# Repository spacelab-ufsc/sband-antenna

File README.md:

<h1 align="center">
	S-Band Antenna Project
	<br>
</h1>

<p align="center">

</p>

<details>
    <summary><b>Summary</b></summary>
    <ol>
        <li>
            <a href="#overview">Overview</a>
        </li>
        <li>
            <a href="#repository-organization">Repository Organization</a>
        </li>
        <li>
            <a href="#license">License</a>
        </li>
        <li>
            <a href="#releases">Releases</a>
        </li>
        <li>
            <a href="#notes">Notes</a>
        </li>
        <li>
            <a href="#references">References</a>
        </li>
    </ol>
</details>

## Overview
​The S-Band Antenna project consists of developing an antenna for the S-Band frequency (2.200-2.290 GHz), which its initial goal is to be used in a mission of Radio Occultation for the downlink of data.​

<!-- 

-->

<p align="center">

</p>

## Repository Organization
`hardware`: Main files of the hardware of the GNSS Active Antenna project.

`docs`: Technical documentation (including user guide and datasheet)

## License
This project is open-source under the following license: CERN Open Hardware License v2.0 (CERN‑OHL‑P v2).

## Releases

Releases are published after ensuring that the project itself do not have any major errors and after testing the PCB. Please refer to the **documentation** for more details.

## Notes
For more info about the SpaceLab, access our [GitHub](https://github.com/spacelab-ufsc/spacelab), [Linkedin](https://br.linkedin.com/company/spacelab-ufsc) or our [website](https://spacelab.ufsc.br/en/home/).

## References

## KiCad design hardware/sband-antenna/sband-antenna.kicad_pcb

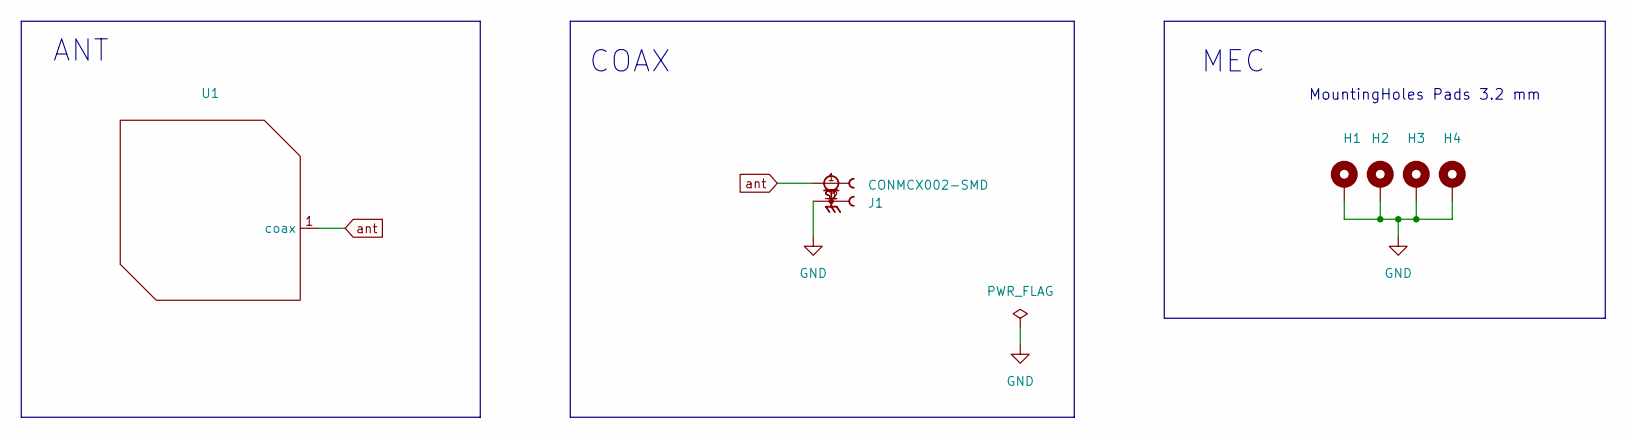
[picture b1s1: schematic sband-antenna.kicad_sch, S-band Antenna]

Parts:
H1, H2, H3, H4: MountingHole_Pad; MountingHole_3.2mm_M3_DIN965_Pad
J1: CONMCX002-SMD; LINX_CONMCX002-SMD
U1: s-band-patch

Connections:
GND: H1.1, H2.1, H3.1, H4.1, J1.S1, J1.S2
ant: J1.1, U1.1 (coax)

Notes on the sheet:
MountingHoles Pads 3.2 mm
ANT
MEC
COAX

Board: 2 copper layers, 6 parts (1 on the bottom side), 2 nets, no tracks yet.

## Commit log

2024-03-27 hardware
2025-04-24 main: hardware: sband antenna project begin
2025-04-24 main: README.md: Added project description
2025-04-27 Atualizado
2025-04-29 Patch and general project updates
2025-04-29 main: Small adjustments
2025-04-29 main: docs folder added
2025-04-29 main: README.md: link to antenna pictures added
2025-04-29 main: docs: cropped images
2025-05-02 main: README.md: repositorio link updated
2025-05-02 main: hardware: sband antenna layout updated
2025-05-03 main: .gitignore file adde
2025-05-04 main: hardware: Frequency band adjustments
2025-05-06 main: hardware: Front mask adjusted
2025-12-10 main: docs: presentation added
